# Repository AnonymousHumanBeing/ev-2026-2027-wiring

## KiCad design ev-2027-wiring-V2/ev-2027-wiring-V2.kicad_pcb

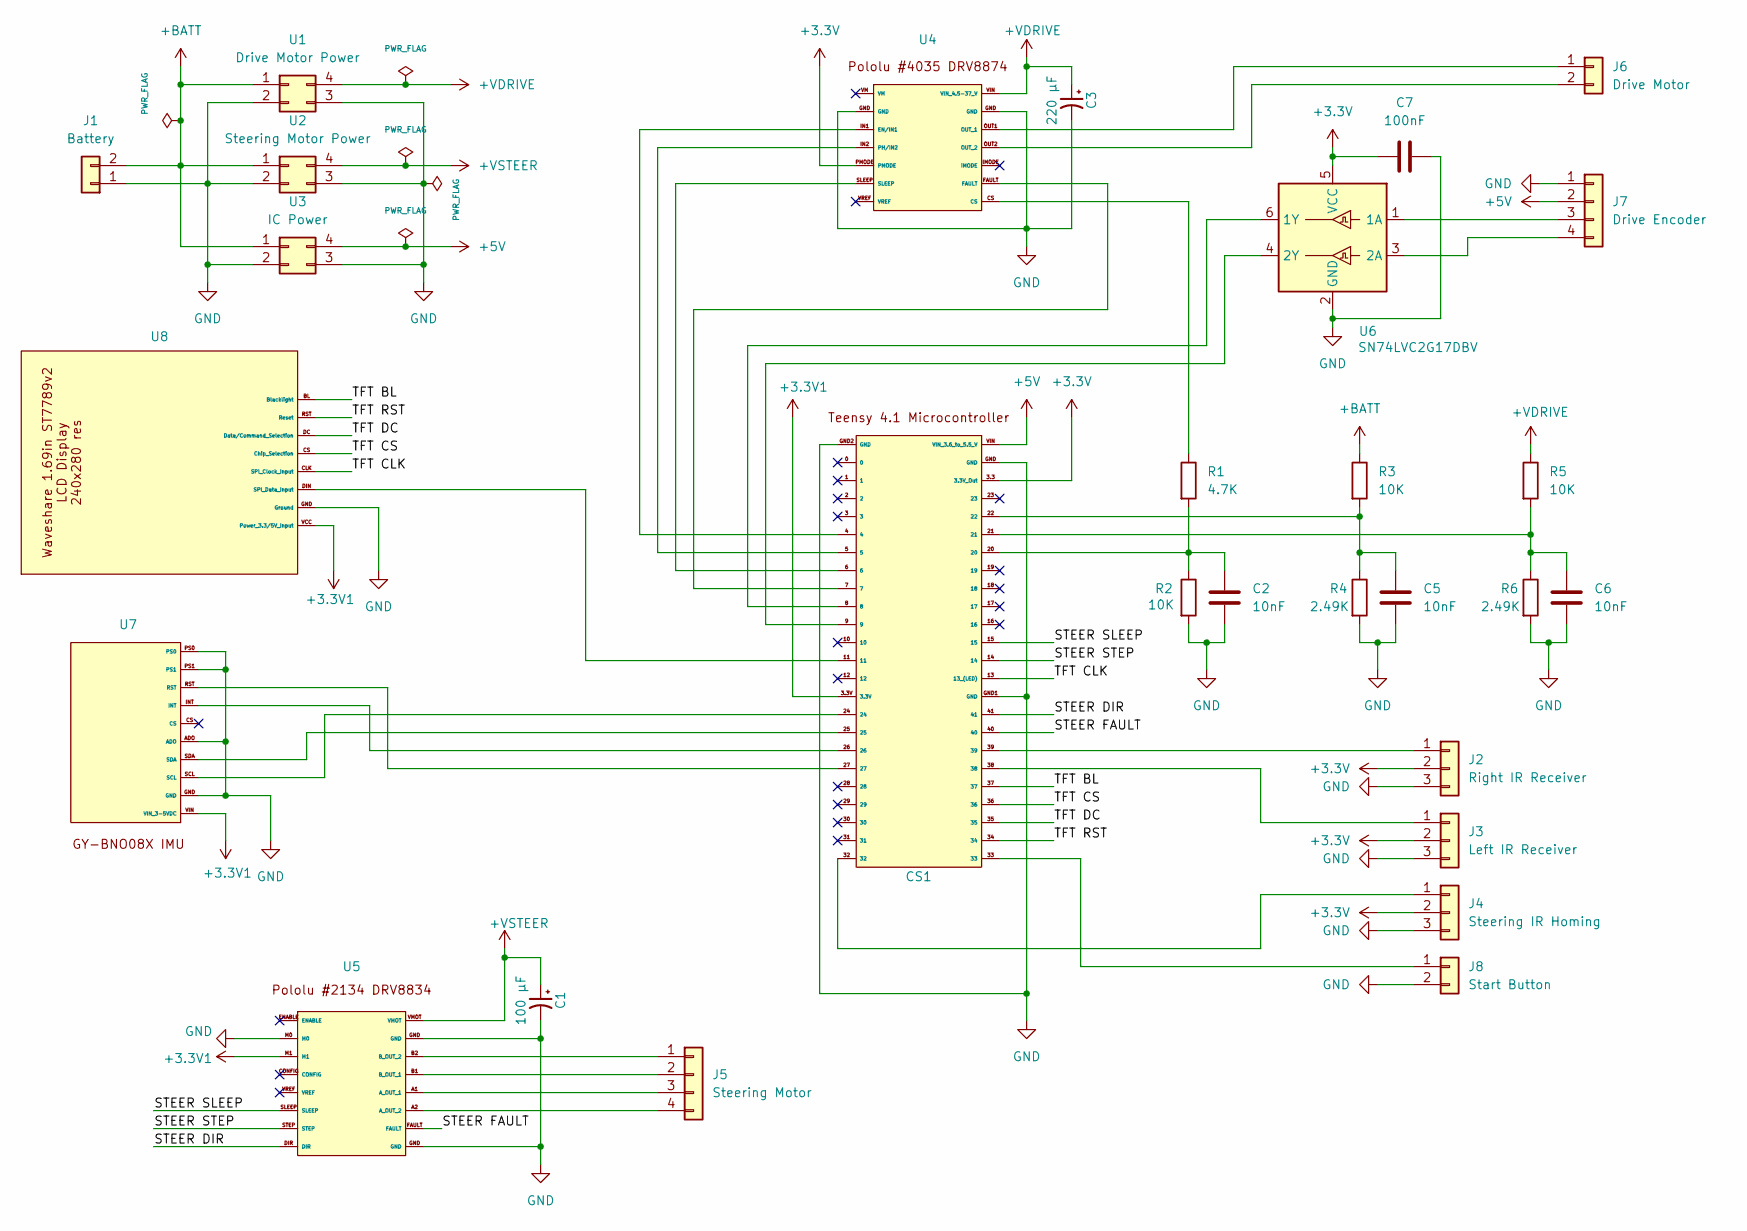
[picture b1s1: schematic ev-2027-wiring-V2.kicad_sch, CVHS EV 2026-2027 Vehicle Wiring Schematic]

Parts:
C1: 100 µF; CP_Radial_D6.3mm_P2.50mm
C2, C5, C6: 10nF; C_Disc_D3.0mm_W1.6mm_P2.50mm
C3: 220 µF; CP_Radial_D8.0mm_P3.50mm
C7: 100nF; C_Disc_D3.0mm_W1.6mm_P2.50mm
CS1: Teensy41_PinNames_GND12
J1: Battery; JST_VH_B2PS-VH_1x02_P3.96mm_Horizontal
J2: Right IR Receiver; JST_XH_S3B-XH-A_1x03_P2.50mm_Horizontal
J3: Left IR Receiver; JST_XH_S3B-XH-A_1x03_P2.50mm_Horizontal
J4: Steering IR Homing; JST_XH_S3B-XH-A_1x03_P2.50mm_Horizontal
J5: Steering Motor; JST_XH_S4B-XH-A_1x04_P2.50mm_Horizontal
J6: Drive Motor; JST_VH_B2PS-VH_1x02_P3.96mm_Horizontal
J7: Drive Encoder; JST_XH_S4B-XH-A_1x04_P2.50mm_Horizontal
J8: Start Button; JST_XH_S2B-XH-A_1x02_P2.50mm_Horizontal
R1: 4.7K; R_Axial_DIN0207_L6.3mm_D2.5mm_P7.62mm_Horizontal
R2, R3, R5: 10K; R_Axial_DIN0207_L6.3mm_D2.5mm_P10.16mm_Horizontal
R4, R6: 2.49K; R_Axial_DIN0207_L6.3mm_D2.5mm_P10.16mm_Horizontal
U1: Drive Motor Power; Buck_LM2596_Module_Numbered
U2: Steering Motor Power; Buck_5V_Mini_17.5x12.3mm_Numbered
U3: IC Power; Buck_5V_Mini_17.5x12.3mm_Numbered
U4: Pololu_DRV8874_4035
U5: Pololu_DRV8834_2134
U6: SN74LVC2G17DBV; SOT-23-6_SN74LVC2G17DBV
U7: GY-BNO08X_1x10_P2.54mm
U8: Display_ST7789_Header_1x08_P2.54mm_Named

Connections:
+3.3V: C7.1, CS1.3.3 (3.3V_Out), J2.2, J3.2, J4.2, U4.PMODE, U6.5 (VCC)
+3.3V1: CS1.3.3V, U5.M1, U7.VIN (VIN_3-5VDC), U8.VCC (Power_3.3/5V_Input)
+5V: CS1.VIN (VIN_3.6_to_5.5_V), J7.2, U3.4
+BATT: J1.2, R3.1, U1.1, U2.1, U3.1
+VDRIVE: C3.1, R5.1, U1.4, U4.VIN (VIN_4.5-37_V)
+VSTEER: C1.1, U2.4, U5.VMOT
/STEER DIR: CS1.41, U5.DIR
/STEER FAULT: CS1.40, U5.FAULT
/STEER SLEEP: CS1.15, U5.SLEEP
/STEER STEP: CS1.14, U5.STEP
/TFT BL: CS1.37, U8.BL (Blacklight)
/TFT CLK: CS1.13 (13_(LED)), U8.CLK (SPI_Clock_Input)
/TFT CS: CS1.36, U8.CS (Chip_Selection)
/TFT DC: CS1.35, U8.DC (Data/Command_Selection)
/TFT RST: CS1.34, U8.RST (Reset)
GND: C1.2, C2.2, C3.2, C5.2, C6.2, C7.2, CS1.GND, CS1.GND1 (GND), CS1.GND2 (GND), J1.1, J2.3, J3.3, J4.3, J7.1, J8.2, R2.2, R4.2, R6.2, U1.2, U1.3, U2.2, U2.3, U3.2, U3.3, U4.GND, U5.GND, U5.M0, U6.2 (GND), U7.ADO, U7.GND, U7.PS0, U7.PS1, U8.GND (Ground)
unnamed: C2.1, CS1.20, R1.2, R2.1
unnamed: C5.1, CS1.22, R3.2, R4.1
unnamed: C6.1, CS1.21, R5.2, R6.1
unnamed: CS1.6, U4.SLEEP
unnamed: CS1.7, U4.FAULT
unnamed: CS1.24, U7.SCL
unnamed: CS1.25, U7.SDA
unnamed: CS1.26, U7.INT
unnamed: CS1.27, U7.RST
unnamed: CS1.39, J2.1
unnamed: CS1.38, J3.1
unnamed: CS1.32, J4.1
unnamed: J5.1, U5.B2 (B_OUT_2)
unnamed: J5.2, U5.B1 (B_OUT_1)
unnamed: J5.3, U5.A1 (A_OUT_1)
unnamed: J5.4, U5.A2 (A_OUT_2)
unnamed: J6.1, U4.OUT1 (OUT_1)
unnamed: J6.2, U4.OUT2 (OUT_2)
unnamed: J7.3, U6.1 (1A)
unnamed: J7.4, U6.3 (2A)
unnamed: CS1.33, J8.1
unnamed: R1.1, U4.CS
unnamed: CS1.4, U4.IN1 (EN/IN1)
unnamed: CS1.5, U4.IN2 (PH/IN2)
unnamed: CS1.8, U6.6 (1Y)
unnamed: CS1.9, U6.4 (2Y)
unnamed: CS1.11, U8.DIN (SPI_Data_Input)

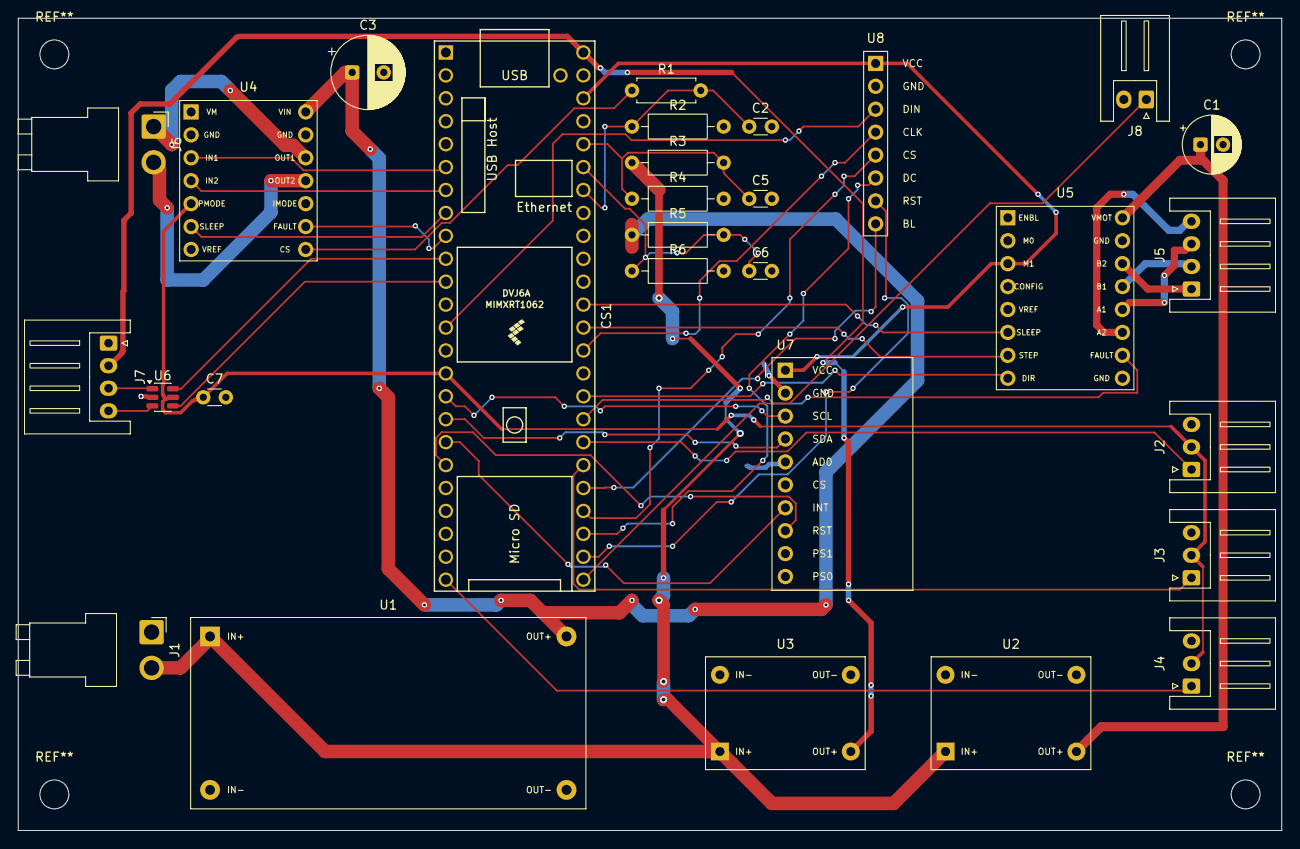
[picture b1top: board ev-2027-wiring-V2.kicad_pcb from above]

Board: 2 copper layers, 140.0 x 90.0 mm, 29 parts (0 on the bottom side), 43 nets.

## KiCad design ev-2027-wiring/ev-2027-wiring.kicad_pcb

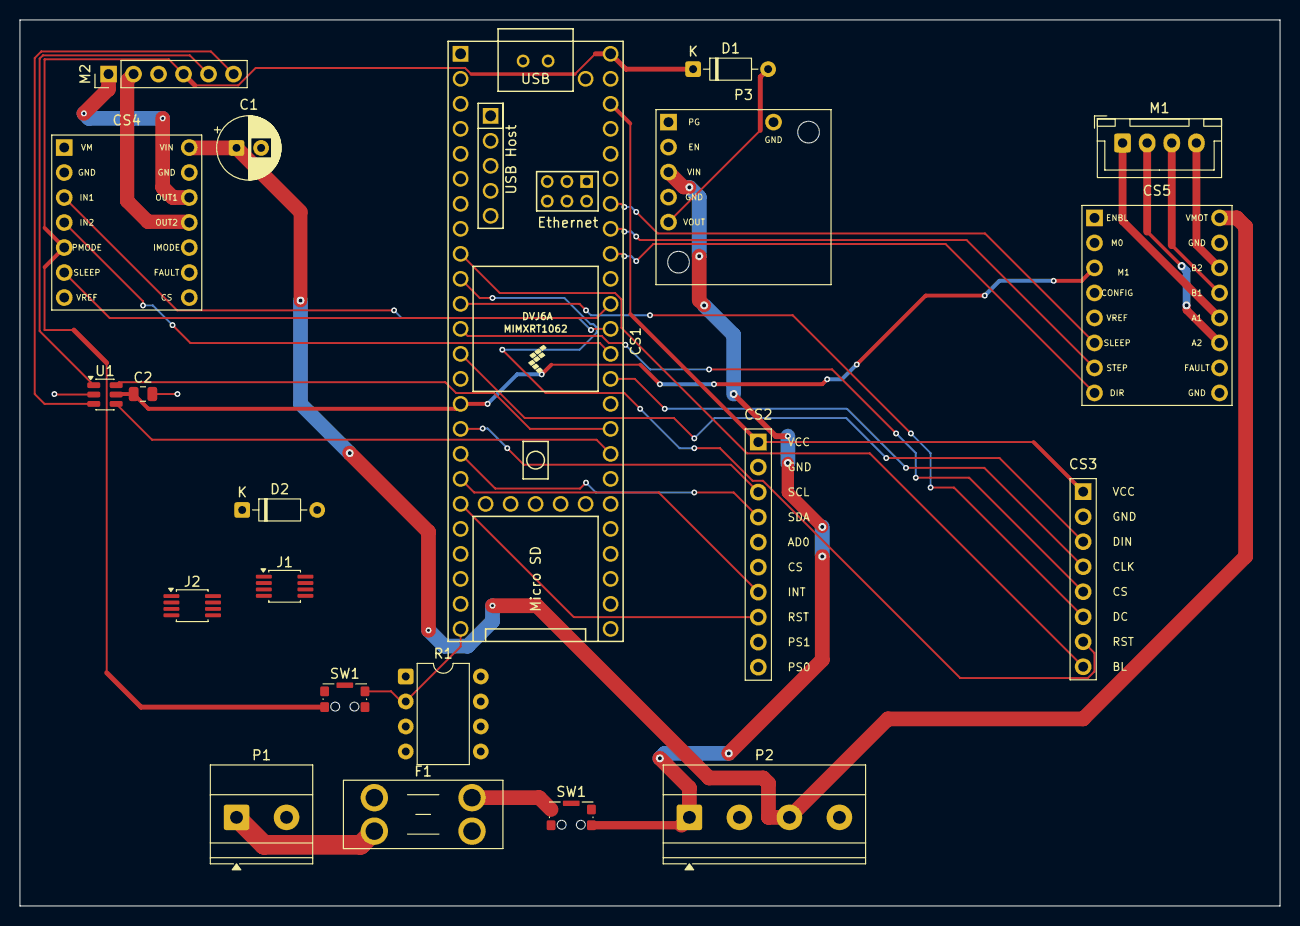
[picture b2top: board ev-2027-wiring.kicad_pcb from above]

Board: 2 copper layers, 128.0 x 90.0 mm, 21 parts (0 on the bottom side), 41 nets.

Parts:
C1: 100 µF; CP_Radial_D6.3mm_P2.50mm
C2: 0.1 µF; C_0805_2012Metric
CS1: Teensy41_PinNames
CS2: GY-BNO08X_1x10_P2.54mm
CS3: Display_ST7789_Header_1x08_P2.54mm_Named
CS4: Pololu_DRV8874_4035
CS5: Pololu_DRV8834_2134
D1: D; D_DO-35_SOD27_P7.62mm_Horizontal
D2: 1N4004; D_DO-35_SOD27_P7.62mm_Horizontal
F1: Fuse 5A; Fuseholder_Blade_Mini_Keystone_3568
J1: 5V Voltage Regultor; MSOP-8_3x3mm_P0.65mm
J2: 8V Voltage Regultor; MSOP-8_3x3mm_P0.65mm
M1: NEMA8_Stepper_JST_XH_1x04
M2: Pololu_25D_Motor_Encoder_Header_1x06
P1: Battery_ScrewTerminal_1x02_P5.08mm
P2: Reg8V_ScrewTerminal_1x04_P5.08mm
P3: Pololu_D24V22F5_2858
R1: 10k Ω; DIP-8_W7.62mm
SW1: SW_DIP_x01; SW_SPST_CK_KMS2xxGP
SW1#2: SW_Push; SW_SPST_CK_KMS2xxGP
U1: SN74LVC2G17DBV; SOT-23-6

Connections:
+3.3V: CS1.3.3 (3.3V_Out), CS4.PMODE, M2.Blue (encoder_vcc_3.5-20V), U1.5 (V_{CC})
+3.3V1: CS1.3.3V, CS2.VIN (VIN_3-5VDC), CS3.VCC (Power_3.3/5V_Input), CS5.M1
+5V: CS1.VIN (VIN_3.6_to_5.5_V), D2.1 (K)
+8V: C1.1, CS4.VIN (VIN_4.5-37_V), CS5.VMOT, J2.4
GND: C1.2, CS1.GND, CS2.ADO, CS2.GND, CS2.PS0, CS2.PS1, CS3.GND (Ground), CS4.GND, CS5.GND, CS5.M0, J1.3, J2.3, M2.Green (encoder_GND), SW1#2.2, U1.2 (GND)
unnamed: CS1.13 (13_(LED)), CS3.CLK (SPI_Clock_Input)
unnamed: CS1.6, CS4.SLEEP
unnamed: CS1.23, CS4.FAULT
unnamed: CS1.24, CS2.SCL
unnamed: CS1.25, CS2.SDA
unnamed: CS1.26, CS2.INT
unnamed: CS1.27, CS2.RST
unnamed: CS1.28, CS5.STEP
unnamed: CS1.29, CS5.DIR
unnamed: CS1.30, CS5.SLEEP
unnamed: CS1.31, CS5.FAULT
unnamed: CS1.33, SW1#2.1
unnamed: CS1.7, CS3.BL (Blacklight)
unnamed: CS1.10, CS3.CS (Chip_Selection)
unnamed: CS1.9, CS3.DC (Data/Command_Selection)
unnamed: C2.2, P2.GND, P3.GND, R1.1
unnamed: CS1.8, CS3.RST (Reset)
unnamed: CS1.11, CS3.DIN (SPI_Data_Input)
unnamed: CS1.4, CS4.IN1 (EN/IN1)
unnamed: CS4.OUT1 (OUT_1), M2.Red (motor_power)
unnamed: CS4.OUT2 (OUT_2), M2.Black (motor_power)
unnamed: CS1.5, CS4.IN2 (PH/IN2)
unnamed: CS5.A1 (A_OUT_1), M1.A (A1_Black)
unnamed: CS5.A2 (A_OUT_2), M1.C (A2_Green)
unnamed: CS5.B1 (B_OUT_1), M1.B (B1_Red)
unnamed: CS5.B2 (B_OUT_2), M1.D (B2_Blue)
unnamed: D1.2 (A), P3.VOUT (VOUT_5V)
unnamed: D2.2 (A), J1.4
unnamed: F1.2, SW1.1
unnamed: J1.1, J2.1, P1.VOUT (raw_battery_output_12V)
unnamed: J1.2, J2.2, P1.GND
unnamed: M2.Yellow (encoder_A_output), U1.1 (1A)
unnamed: M2.White (encoder_B_output), U1.3 (2A)
unnamed: P2.VIN, P3.VIN (VIN_4-36V), SW1.2
unnamed: CS1.3, U1.6 (1Y)
unnamed: CS1.2, U1.4 (2Y)
